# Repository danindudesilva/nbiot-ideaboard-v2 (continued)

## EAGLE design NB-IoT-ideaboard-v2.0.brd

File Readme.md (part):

# Ideamart NB-IoT Ideaboard
###### version 2.0

## Introduction

Ideamart NB-IoT Ideaboard is a connected battery-powered quick-prototyping board created for IoT developers and makers. Its purpose is to make IoT device developemtn process quick and easy as possible. It has communication interfaces such as I2C, SPI, USART, CAN, along with a 12-bit ADC and 16-bit PWM pins broken out with power supply pins, so that any sensor/actuator module in the market can be hooked up to it easily wihout hassle.

It is powered by a 3.7V Li-Ion cell which is managed by an onboard Li-Ion charge controller, making it ideal for prototyping IoT devices. Its main MCU is a powerful STM32F103R series microcontroller with 128K Flash and 20K SRAM memory, enough to make any IoT application effortlessly. It can be connected to the NB-IoT network via a Quectel BC92 modem with 2G GSM fallback option while supporting MFF2 or 3FF eSIM giving it full internet access. 

View 3d model: https://a360.co/3fFFWQ6

## Features
The Ideaboard offers the following features
1.	STM32F103RB microcontroller in LQFP64 package with pin compatibility to any other STM32F103R series microcontroller
2.	Onboard Quectel BC92 BN-IoT modem with 2G GSM fallback
	- LTE Cat NB2: B3/B5/B8/B20/B28
	- GSM: 850/900/1800/1900 MHz
3.	Lithium-Ion cell as primary power supply and onboard Li-Ion management 
    - A 3.7V 2400mAh Li-Ion cell is used to directly power the BC92 modem and the microcontroller
    - Single cell Li-Ion battery management unit for safe charge/discharge of the Li-Ion cell
4.	Flexible power outputs
    - 3.3V power output for basic sensor/actuator power (max usage: 400mA)
    - Optional 5V power output boosted from the 3.7V Li-Ion cell for 5V applications (not available by default)
    - VBUS pins connected to the USB VBUS rail to supply power to the board
5.	External power supply
    - Micro USB port for easy power supply connection
    - External DC 5V source for 2.1 DC connector
6.	Power management access point
    - Connector to an external current meter/ammeter to measure the amount of power drawn from the Li-Ion cell to the Ideaboard
7.	SWD or UART programming
    - Onboard boot mode selection for switching between programming modes
8.	4 LEDs: PWR, USR, NET, and CHG
    - PWR: Board power on indicator
    - USER: User configurable LED
    - NET: BC92 Modem Network status indicator
    - CHG: Li-Ion cell charging indicator
9.	4 pushbuttons: NRST, USER, RESET, PWRKEY
    - NRST: STM32F103RB microcontroller Reset button
    - USER: User configurable pushbutton for input
    - RESET: BC92 modem reset button
    - PWRKEY: BC92 modem power on/off button
10.	Pinheaders to access GPIOs
    - ADC12 IN: 6 GPIOs for 12—bit ADC input
    - I2C 1: GND, SCL, SDA, 3V3 pins for I2C 1 port
    - CAN 1: GND, TX, RX, 3V3 pins for CAN bus port
    - USART 1: VBUS, TXD, RXD, GND, 3V3 pins for USART 1 port
    - SPI 1: 3V3, SCK, MISO, MOSI, NSS, GND pins for SPI 1 interface
    - SPI 2: GND, NSS, MOSI, MISO, SCK, 3V3 pins for SPI 1 interface
    - SWD: SWDIO, GND, SWCLK, 3V3, NRST, SWD pins for SWD programming/debug interface
    - Other GPIOs: A mix of digital and analog I/O pins with no specific assignment for general I/O purposes
11.	Debug UART port for BC92 modem
    - Debug port with VBUS, GND, RX, and TX pins to access the debug COM port of the BC92 modem
12.	eSIM technology or MircoSim compatibility
    - Onboard eSIM MFF2 chip or microsim connector for SIM connection whichever can be used according to user preference
13.	IPEX/u.FL antenna connector for BC92 modem RF antenna
    - Impedance matched to 50 Ohms with optional “PI” type matching circuit reserved for antenna optimization

## STM32F103RB Microcontroller

The STM32F103RB microcontroller is a medium-density performance line family incorporating the high-performance ARM®Cortex®-M3 32-bit RISC core operating at a 72 MHz frequency, high-speed embedded memories with 128K Flash and 20K SRAM (covering from 16 Kbytes to 1 Mbyte of Flash in the STM32F130R line) and an extensive range of enhanced I/Os and peripherals connected to two APB buses. 
All devices in the family offer two 12-bit ADCs, three general purpose 16-bit timers plus one PWM timer, as well as standard and advanced communication interfaces: up to two I2Cs and SPIs, three USARTs, an USB and a CAN.
Key Features
1. ARM 32-bit Cortex -M3 CPU Core
    - 72 MHz maximum frequency,1.25 DMIPS/MHz (Dhrystone 2.1) performance at 0 wait state memory access
    - Single-cycle multiplication and hardware division
2. Memories
    - 128 Kbytes of Flash memory
    - 20 Kbytes of SRAM
    - Clock, reset and supply management
3. 2.0 to 3.6 V application supply and I/Os
    - POR, PDR, and programmable voltage detector (PVD)
    - 8 MHz crystal oscillator
    - Internal 8 MHz factory-trimmed RC
    - Internal 40 kHz RC
    - PLL for CPU clock
    - 32 kHz oscillator for RTC with calibration
4. Low power
    - Sleep, Stop and Standby modes
5. 2 x 12-bit, 1 μs A/D converters
    - Conversion range: 0 to 3.6 V
    - Dual-sample and hold capability
    - Temperature sensor
6. DMA
    - 7-channel DMA controller
    - Peripherals supported: timers, ADC, SPIs, I2Cs and USARTs
7. Debug mode
    - Serial wire debug (SWD)
8. 7 timers
    - Three 16-bit timers, each with up to 4 IC/OC/PWM or pulse counter and quadrature (incremental) encoder input
    - 16-bit, motor control PWM timer with dead-time generation and emergency stop
    - 2 watchdog timers (Independent and Window)
    - SysTick timer 24-bit downcounter
9. Communication interfaces
    - I2C interfaces (SMBus/PMBus)
    - USARTs (ISO 7816 interface, LIN, IrDA capability, modem control)
    - SPIs (18 Mbit/s)
10. CAN interface (2.0B Active)
    - CRC calculation unit, 96-bit unique ID

## Quectel BC92 NB-IoT/GSM modem

BC92 is a high-performance, multi-band NB-IoT/GSM dual-mode module with extremely low power consumption. Designed to be compatible with Quectel GSM/GPRS M95 module, NB-IoT BC95-G module and LPWA BG95 module, BC92 provides abundant external interfaces and protocol stacks, providing great convenience for customers' applications.
BC92 supports 3GPP R13 and R14. Its general features are shown below.
- Support GSM850, EGSM900, DCS1800 and PCS1900
- Support GPRS data transmission and GSM SMS service
- Designed with power-saving technology, the current consumption is as low as 4 μA in deep sleep mode
- Integrate various Internet service protocols (TCP, UDP, PPP, FTP, HTTP(S)
- Support extended AT commands

The frequency bands supported by BC92 are listed below.
- LTE Cat NB2: B3/B5/B8/B20/B28
- GSM: 850/900/1800/1900 MHz

BC92 is an SMD type module with 50 LCC pins, which can be embedded into a variety of data transmission applications with a compact profile of 23.6 mm ×19.9 mm ×2.2 mm, BC92 can meet almost all requirements for M2M applications, such as smoke detector, wireless meter reading, bike sharing, smart parking, asset tracking, wearables, etc.

Power Supply
- Supply voltage range: 3.4~4.2 V.
- Typical supply voltage: 3.8 V.
- Deep Sleep Mode Typical current consumption in Deep Sleep Mode: 4 μA

NB-IoT Frequency Bands
- B3/B5/B8/B20/B28

NB-IoT transmitting power
- 23 dBm ±2 dB

For more information on the STM32F103RB microcontroller or the Quectel BC92 modem, please visit www.st.com or https://www.quectel.com/product/bc92.htm

## QuickStart

The Ideamart NB-IoT Ideaboard is a low-cost and easy-to-use IoT prototyping platform designed for IoT developers and makers which can be used to quickly test and implement a connected IoT solution.  

### Getting started

Follow the sequence below to configure and power up the Ideaboard

1. Make sure a 3.7V Li-Ion battery is connected to the LIPO connector

2. Check the jumper positions on the board
    - Make sure JP1 jumper near the LIPO connector is connected
    - Make sure all 5 of MODEMCTL jumpers are connected parallel to the length of the board
    - Position of the B1 and B0 jumpers of the BOOT MODE selector. (Refer the table on the board or this document to select the boot mode according to your programming preference)

3. Connect the Ideaboard to a PC or a 5V power adapter with a micro USB cable through the POWER USB connector or using a 5V DC power supply through to the 2.1mm barrel connector on the bottom side of the board. The CHG LED will turn on indicating that the Li-Ion cell is charging. 

4. Turn the power switch on. The PWR LED will turn on indicating that Ideaboard is getting power from the Li-Ion cell.

## Hardware layout and configuration

The Ideaboard is designed around the STM32F103RB MCU in a 64-pin LQFP package as the main controller.

### Hardware block diagram

#### Top Layout

#### Bottom Layout

### Ideaboard mechanical dimensions

### Pinout Diagram

### Power supply and Battery Management

The Ideaboard’s main power supply is it’s 3.7V Li-Ion cell. It must always be connected although an external power source is used. The external power supply charges the Li-Ion cell while the cell powers the board. 
The power switch must be turned on to get power to the board. Then the PWR LED will turn on.  When as external power supply is connected, the battery will start charging and it will be indicated by the CHG LED. 
The external power supply must be 5V and can be connected to the POWER micro USB port or the 5V DC input jack on the bottom side of the PCB.

The 3.3V rail is powered by a 3.3V LDO which is directly connected to the Li-Ion cell. An optional 5V step-up converter is also powered by the Li-Ion cell for any external 5V peripherals.

#### Powering external peripherals using the Ideaboard

3.3V peripherals can be connected to the 3V3 pins on the Ideaboard for power.For 5V peripherals, the 5V pins on the Ideaboard can be used. These pins will not have power unless the 5V step-up converter on the bottom side of the Ideaboard is soldered. 

The VBUS pins can also be used to provide 5V power to external peripherals, but it is not recommended since the VBUS rail will lose power once the external power is removed, therefore, use the 5V step-up converter. 

All the VBUS pins are connected to the VBUS of the USB port and the positive terminal of the 5V DC input.

#### Using the onboard 5V step-up converter

The 5V step-up converter is soldered by default. Please refer the below table when assembling the parts for the 5V step-up converter.
| Designator | Value | Component | Package | Manufacturer Part # |
| ----------- | ----------- | ----------- |----------- |----------- |
|   U4      |   PAM2401 |   Step-up converter	|   MSOP8	    |PAM2401SCADJ   |
|   C20     |   22uF    |   Ceramic Capacitor   |   0805 SMD    |   -           |
|   C21     |   22uF    |   Ceramic Capacitor   |   0805 SMD    |   -           |
|   R14     |   750k    |   Resistor            |   0805 SMD    |   -           |
|   R15     |   750k    |   Resistor            |   0805 SMD    |   -           |
|   R16     |   100k    |   Resistor            |   0805 SMD    |   -           |
|   L2      |   2.2uH/3A|   Inductor            |   4x4mm SMD   |IFSC1515AHER2R2M01|

#### Measuring the Ideaboard’s power consumption

The power consumption can be measured by connecting an ammeter to the JP1 pins on the ideaboard. This will give the current drawn from the Li-Ion cell by the Ideaboard and the connected peripherals. 

Once the current measuring device is removed, the jumper must be put back on the JP1 pins in order for the Ideaboard to work.

#### LEDs and Pushbuttons

The ideaboard has 4 LEDs and 4 pushbuttons 
##### LEDs
- PWR: Power on indicator.
- USR: An LED connected to PB13 pin of the MCU
- CHG: Li-Ion cell charging indicator
- NET: Network status of the BC92 modem

##### Pushbuttons
- USER: A pushbutton connected to PC13 pin of the MCU
- NRST: Reset pin of the STM32F103RB MCU
- PWRKEY: Powerkey button for the BC92 modem. 
- RESET: Reset button for the BC92 modem

### NB-IoT Modem Communication

The STM32F103RB MCU communicates with the Quectel BC92 modem through a UART port. 
The modem is connected to USART3 of the MCU. The control signals to the modem from the MCU are PSM_EINT, POWERKEY, and RESET. 
All the UART and control signals are connected to the MCU via jumpers in case the developer needs to disconnect the modem communication or control signals from the MCU. Please refer the below figure for the connections.

### CC1101 connector

The Ideaboard has a 2.54mm pitch 2x6 female pinheader connector for a CC1101 radio module. This is connected to the MCUs SPI1 port. Please refer below figure for the pin connections.

## Programming the Ideaboard

Ideaboard can be programmed using its SWD or USART1 interface. The 2 programming interfaces are highlighted on the top side of the PCB in white. In order to use either programming mode, the boot mode of the MCU must be selected by setting the B0 and B1 jumpers on BOOT pin header as given in the table below.

| BOOT0 |   BOOT1   | Boot mode         | Aliasing  |
| ----- | --------- | ---------         | --------  |
|  x    |       0   | Main Flash Memory | Main flash memory is selected as boot space   |
|  0    |       1   | System Memory     | System Memory is selected as boot space       |
|  1    |       1   | Embedded SRAM     | Embedded SRAM is selected as boot space       |

### Using the SWD Interface

The main flash memory is used as boot space. To select the boot mode of the MCU, set the BOOT jumpers as below:

````
B0 = 0 and B1 = 0
````

After setting the jumpers Reset the MCU.

When using the SWD interface, an external ST-Link programmer such as ST-Link V2 dongle can be used.

The pins 2, 4, and 6 on the ST-Link V2 programmer should be connected to SWCLK, SWDIO, and GND on the Ideaboard SWD pin header respectively.

### Using the USART 1 Interface

When using the USART1 interface, the boot loader in the system memory must be activated. Set the BOOT jumpers as below. This embedded boot loader is programmed by ST during production.

The system memory is used as boot space. To select the boot mode of the MCU, set the BOOT jumpers as below:
````
B0 = 1 and B1 = 0
````

After setting the jumpers Reset the MCU.

In order to use the USART1 interface, a USB to serial converter should be used by connecting it to the RXD, TXD, and GND pins of the Ideaboard. (The VBUS pin can be used to charge the Li-Ion cell if needed).

After installing the STM32 board definitions, Arduino IDE can be used to program the Ideaboard using the USART1 interface.

### Using the CDC Virtual com port

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
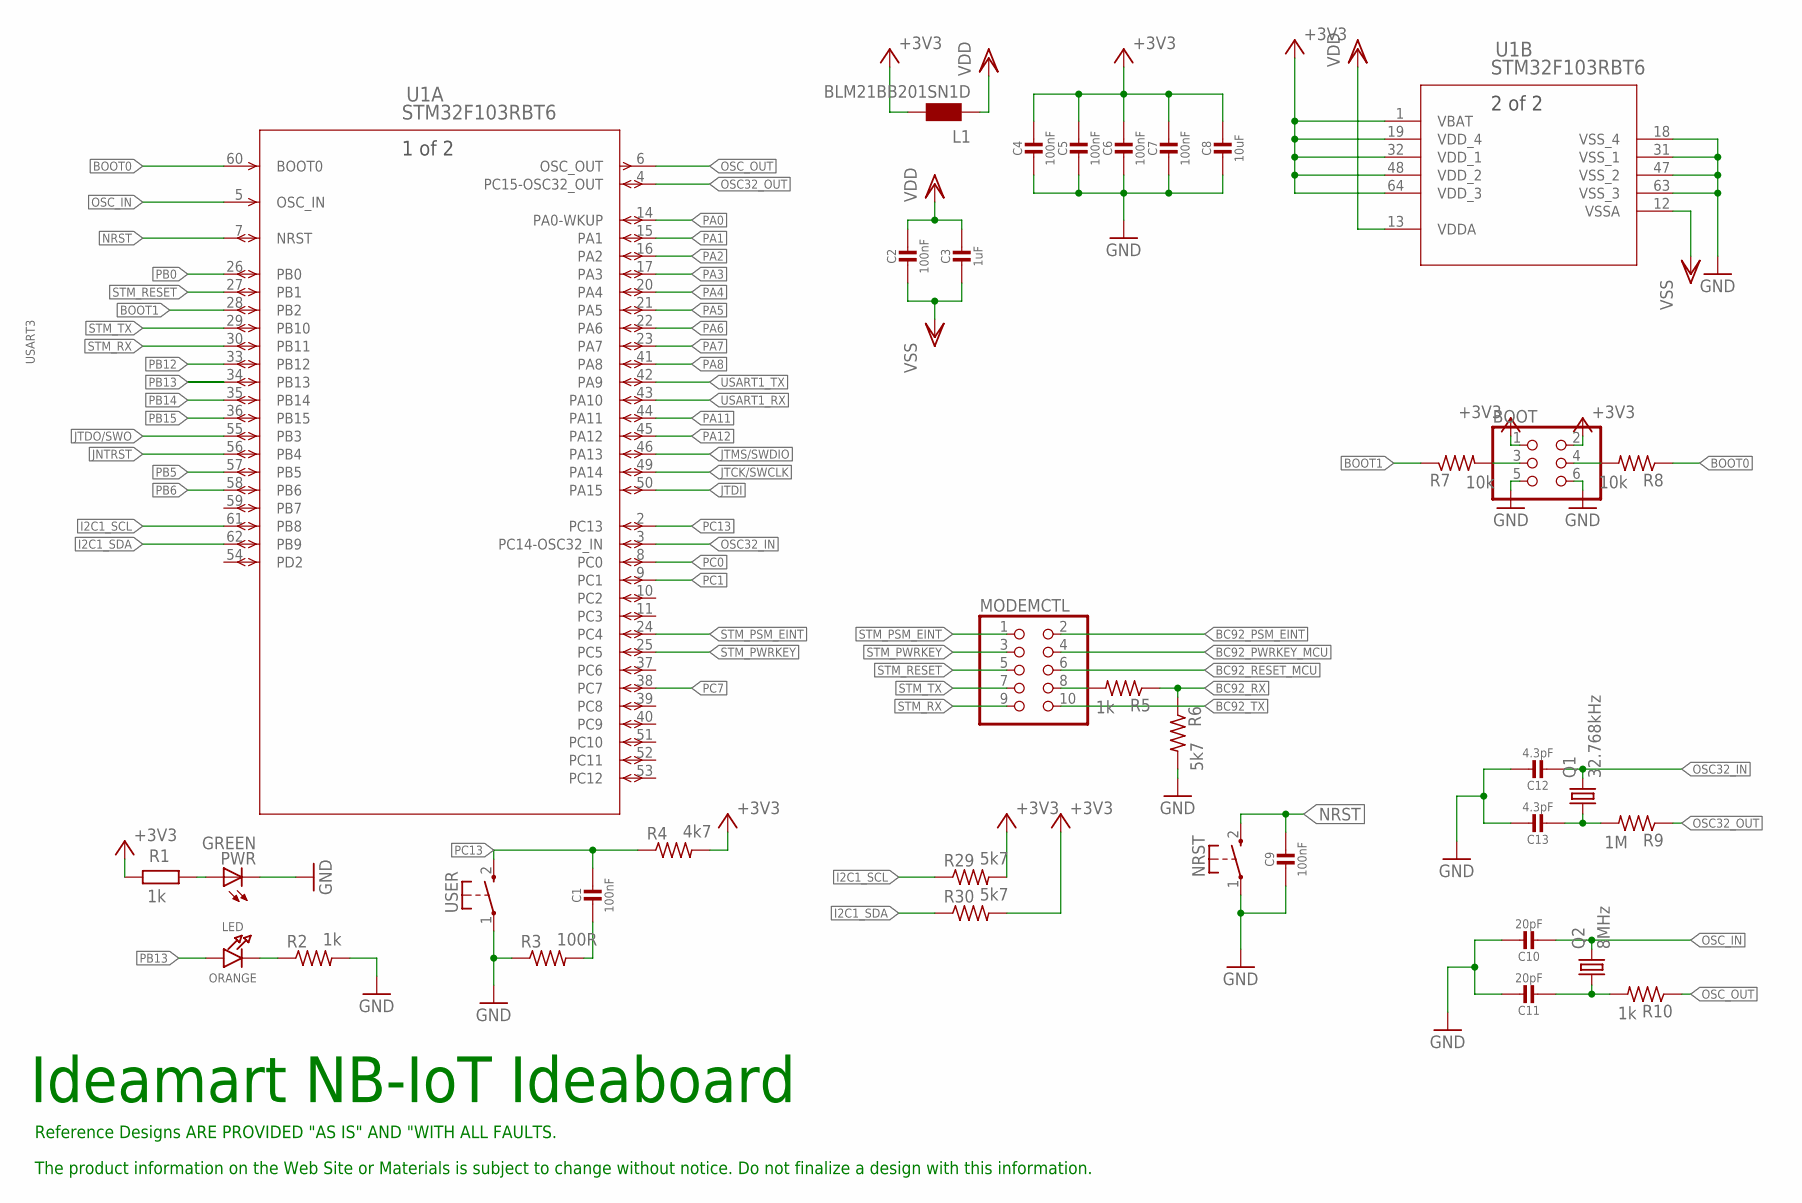
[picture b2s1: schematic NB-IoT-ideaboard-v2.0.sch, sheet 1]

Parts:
BOOT: PINHD-2X03_2.54-SMD; 2X03SMD
C1, C2, C4, C5, C6, C7, C9: 100nF; _0805MP
C3: 1uF; _0805MP
C8: 10uF; _0805MP
C10, C11: 20pF; _0805MP
C12, C13: 4.3pF; _0805MP
L1: BLM21BB201SN1D; 0805
LED: ORANGE; CHIPLED_0805
MODEMCTL: PINHD-2X05_2.54-SMD; 2X05SMD
NRST: KSS-2EG4430
PWR: GREEN; CHIP-LED0805
Q1: 32.768kHz; TC26H-SMD
Q2: 8MHz; SM49
R1: 1k; R0805
R2, R5, R10: 1k; M0805
R3: 100R; M0805
R4: 4k7; M0805
R6, R29, R30: 5k7; M0805
R7, R8: 10k; M0805
R9: 1M; M0805
U1: STM32F103RBT6; LQFP64-10X10MM
USER: KSS-2EG4430

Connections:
+3V3: BOOT.1, BOOT.2, C4.1, C5.1, C6.1, C7.1, C8.1, L1.2, R1.2, R4.2, R29.2, R30.2, U1.1 (VBAT), U1.19 (VDD_4), U1.32 (VDD_1), U1.48 (VDD_2), U1.64 (VDD_3); also elsewhere on the board
BC92_PSM_EINT: MODEMCTL.2; also elsewhere on the board
BC92_PWRKEY_MCU: MODEMCTL.4; also elsewhere on the board
BC92_RESET_MCU: MODEMCTL.6; also elsewhere on the board
BC92_RX: R5.1, R6.1; also elsewhere on the board
BC92_TX: MODEMCTL.10; also elsewhere on the board
BOOT0: R8.1, U1.60 (BOOT0)
BOOT1: R7.1, U1.28 (PB2)
GND: BOOT.5, BOOT.6, C4.2, C5.2, C6.2, C7.2, C8.2, C9.2, C10.1, C11.1, C12.1, C13.1, NRST.1, PWR.C, R2.2, R3.1, R6.2, U1.18 (VSS_4), U1.31 (VSS_1), U1.47 (VSS_2), U1.63 (VSS_3), USER.1; also elsewhere on the board
I2C1_SCL: R29.1, U1.61 (PB8); also elsewhere on the board
I2C1_SDA: R30.1, U1.62 (PB9); also elsewhere on the board
JNTRST: U1.56 (PB4); also elsewhere on the board
JTCK/SWCLK: U1.49 (PA14); also elsewhere on the board
JTDI: U1.50 (PA15)
JTDO/SWO: U1.55 (PB3); also elsewhere on the board
JTMS/SWDIO: U1.46 (PA13); also elsewhere on the board
unnamed: BOOT.3, R7.2
unnamed: PWR.A, R1.1
unnamed: C11.2, Q2.1, R10.2
unnamed: C13.2, Q1.P$1 (1), R9.2
unnamed: C1.2, R3.2
unnamed: BOOT.4, R8.2
unnamed: LED.C, R2.1
unnamed: MODEMCTL.8, R5.2
NRST: C9.1, NRST.2 (S), U1.7 (NRST); also elsewhere on the board
OSC32_IN: C12.2, Q1.P$2 (2), U1.3 (PC14-OSC32_IN)
OSC32_OUT: R9.1, U1.4 (PC15-OSC32_OUT)
OSC_IN: C10.2, Q2.2, U1.5 (OSC_IN)
OSC_OUT: R10.1, U1.6 (OSC_OUT)
PA0: U1.14 (PA0-WKUP); also elsewhere on the board
PA1: U1.15 (PA1); also elsewhere on the board
PA2: U1.16 (PA2); also elsewhere on the board
PA3: U1.17 (PA3); also elsewhere on the board
PA4: U1.20 (PA4); also elsewhere on the board
PA5: U1.21 (PA5); also elsewhere on the board
PA6: U1.22 (PA6); also elsewhere on the board
PA7: U1.23 (PA7); also elsewhere on the board
PA8: U1.41 (PA8); also elsewhere on the board
PA11: U1.44 (PA11); also elsewhere on the board
PA12: U1.45 (PA12); also elsewhere on the board
PB0: U1.26 (PB0); also elsewhere on the board
PB5: U1.57 (PB5); also elsewhere on the board
PB6: U1.58 (PB6); also elsewhere on the board
PB12: U1.33 (PB12); also elsewhere on the board
PB13: LED.A, U1.34 (PB13); also elsewhere on the board
PB14: U1.35 (PB14); also elsewhere on the board
PB15: U1.36 (PB15); also elsewhere on the board
PC0: U1.8 (PC0); also elsewhere on the board
PC1: U1.9 (PC1); also elsewhere on the board
PC7: U1.38 (PC7); also elsewhere on the board
PC13: C1.1, R4.1, U1.2 (PC13), USER.2 (S)
STM_PSM_EINT: MODEMCTL.1, U1.24 (PC4)
STM_PWRKEY: MODEMCTL.3, U1.25 (PC5)
STM_RESET: MODEMCTL.5, U1.27 (PB1)
STM_RX: MODEMCTL.9, U1.30 (PB11)
STM_TX: MODEMCTL.7, U1.29 (PB10)
USART1_RX: U1.43 (PA10); also elsewhere on the board
USART1_TX: U1.42 (PA9); also elsewhere on the board
VDD: C2.1, C3.1, L1.1, U1.13 (VDDA); also elsewhere on the board
VSS: C2.2, C3.2, U1.12 (VSSA)

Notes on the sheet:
Ideamart NB-IoT Ideaboard
Reference Designs ARE PROVIDED "AS IS" AND "WITH ALL FAULTS.
The product information on the Web Site or Materials is subject to change without notice. Do not finalize a design with this information.
USART3

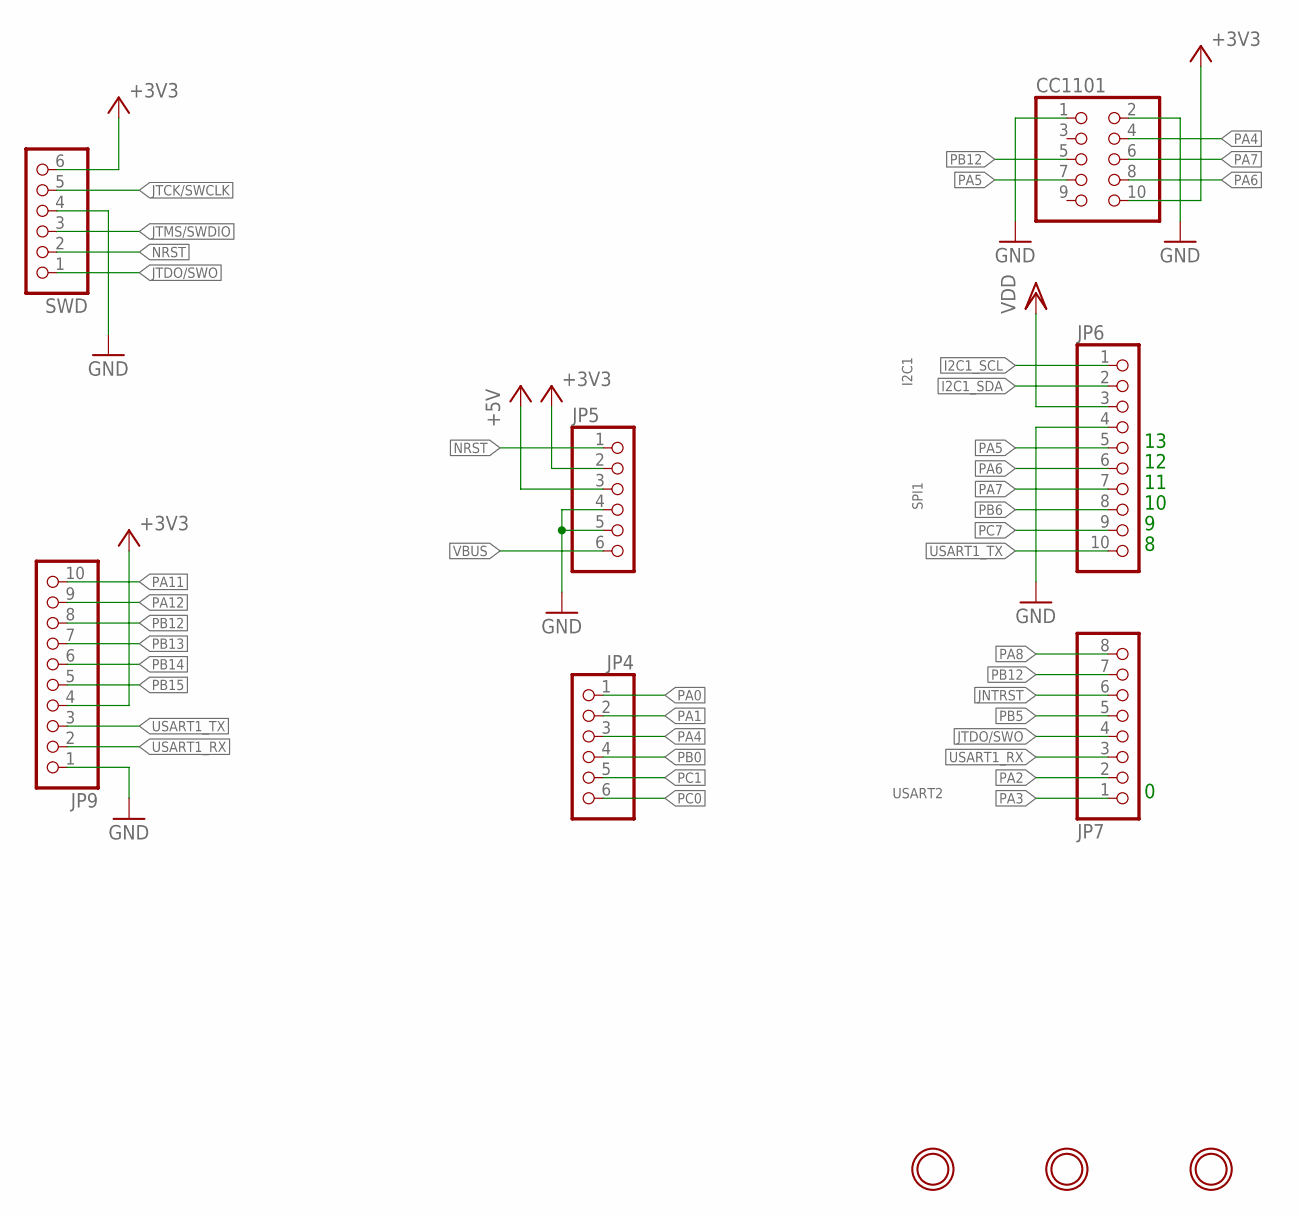
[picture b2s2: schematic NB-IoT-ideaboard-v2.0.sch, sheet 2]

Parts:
$H1, $H2, $H3: MOUNTINGHOLE3.0THIN; MOUNTINGHOLE_3.0_PLATEDTHIN
CC1101: PINHD-2X05_2.54-SMD; 2X05SMD
JP4, JP5: PINHD-1X6; 1X06
JP6: PINHD-1X10; 1X10
JP7: PINHD-1X8; 1X08
JP9: PINHD-1X10_2.54-S; 1X10-S
SWD: PINHD-1X6; 1X06

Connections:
+3V3: CC1101.10, JP5.2, JP9.4, SWD.6; also elsewhere on the board
+5V: JP5.3; also elsewhere on the board
GND: CC1101.1, CC1101.2, JP5.4, JP5.5, JP6.4, JP9.1, SWD.4; also elsewhere on the board
I2C1_SCL: JP6.1; also elsewhere on the board
I2C1_SDA: JP6.2; also elsewhere on the board
JNTRST: JP7.6; also elsewhere on the board
JTCK/SWCLK: SWD.5; also elsewhere on the board
JTDO/SWO: JP7.4, SWD.1; also elsewhere on the board
JTMS/SWDIO: SWD.3; also elsewhere on the board
NRST: JP5.1, SWD.2; also elsewhere on the board
PA0: JP4.1; also elsewhere on the board
PA1: JP4.2; also elsewhere on the board
PA2: JP7.2; also elsewhere on the board
PA3: JP7.1; also elsewhere on the board
PA4: CC1101.4, JP4.3; also elsewhere on the board
PA5: CC1101.7, JP6.5; also elsewhere on the board
PA6: CC1101.8, JP6.6; also elsewhere on the board
PA7: CC1101.6, JP6.7; also elsewhere on the board
PA8: JP7.8; also elsewhere on the board
PA11: JP9.10; also elsewhere on the board
PA12: JP9.9; also elsewhere on the board
PB0: JP4.4; also elsewhere on the board
PB5: JP7.5; also elsewhere on the board
PB6: JP6.8; also elsewhere on the board
PB12: CC1101.5, JP7.7, JP9.8; also elsewhere on the board
PB13: JP9.7; also elsewhere on the board
PB14: JP9.6; also elsewhere on the board
PB15: JP9.5; also elsewhere on the board
PC0: JP4.6; also elsewhere on the board
PC1: JP4.5; also elsewhere on the board
PC7: JP6.9; also elsewhere on the board
USART1_RX: JP7.3, JP9.2; also elsewhere on the board
USART1_TX: JP6.10, JP9.3; also elsewhere on the board
VBUS: JP5.6; also elsewhere on the board
VDD: JP6.3; also elsewhere on the board

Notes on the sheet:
I2C1
SPI1
USART2

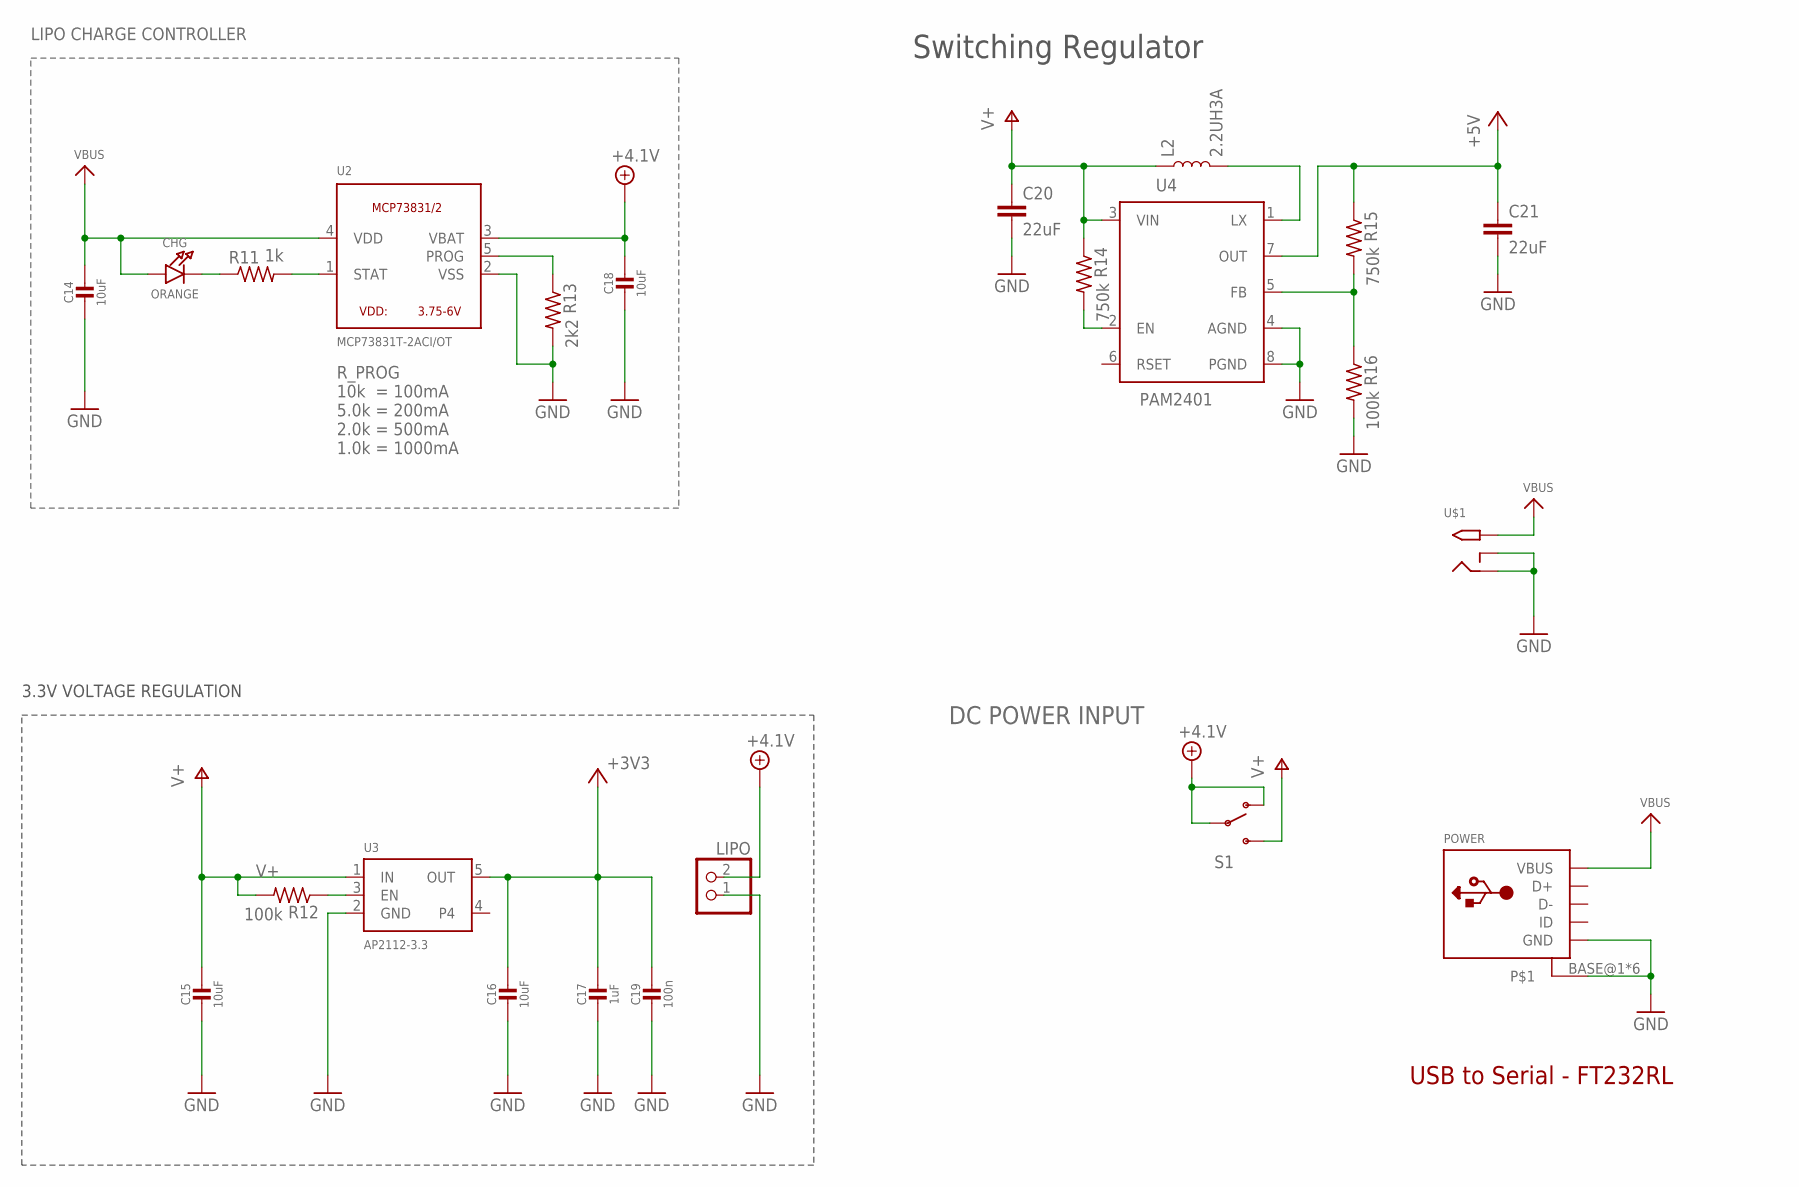
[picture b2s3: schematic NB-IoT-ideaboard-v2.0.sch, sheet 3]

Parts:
C14, C18: 10uF; _0805
C15, C16: 10uF; _0805MP
C17: 1uF; _0805MP
C19: 100n; _0805MP
C20, C21: 22uF; 0805
CHG: ORANGE; CHIPLED_0805
L2: 2.2UH3A; INDUCTOR_4X4MM
LIPO: JST_2PIN-SMT; JST-PH-2-SMT
POWER: USB_MICRO_20329_V2; 4UCONN_20329_V2
R11: 1k; M0805
R12, R16: 100k; M0805
R13: 2k2; M0805
R14, R15: 750k; M0805
S1: SWITCH-SPDT-SMD-A; SWITCH-SPST-SMD-A
U2: MCP73831T-2ACI/OT; SOT23-5
U3: AP2112-3.3; SOT23-5
U4: PAM2401; MSOP8
U$1: 2.1MMJACKSMT; DCJACK_2MM_SMT

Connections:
+3V3: C16.1, C17.1, C19.1, U3.5 (OUT); also elsewhere on the board
+4.1V: C18.1, LIPO.2 (1), S1.1 (O), S1.2, U2.3 (VBAT)
+5V: C21.1, R15.1, U4.7 (OUT); also elsewhere on the board
EN: R14.2, U4.2 (EN)
GND: C14.2, C15.2, C16.2, C17.2, C18.2, C19.2, C20.2, C21.2, LIPO.1 (2), POWER.BASE@1, POWER.BASE@2, POWER.GND, POWER.SPRT@1, POWER.SPRT@2, POWER.SPRT@3, POWER.SPRT@4, R13.2, R16.2, U2.2 (VSS), U3.2 (GND), U4.4 (AGND), U4.8 (PGND), U$1.GND (RING), U$1.GNDBREAK (RING_SW); also elsewhere on the board
unnamed: R12.1, U3.3 (EN)
unnamed: CHG.C, R11.1
unnamed: R11.2, U2.1 (STAT)
unnamed: R13.1, U2.5 (PROG)
unnamed: R15.2, R16.1, U4.5 (FB)
unnamed: L2.P$2 (2), U4.1 (LX)
V+: C15.1, C20.1, L2.P$1 (1), R12.2, R14.1, S1.3 (S), U3.1 (IN), U4.3 (VIN); also elsewhere on the board
VBUS: C14.1, CHG.A, POWER.VBUS, U2.4 (VDD), U$1.PWR2 (TIP); also elsewhere on the board

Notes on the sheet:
USB to Serial - FT232RL
3.3V VOLTAGE REGULATION
R_PROG 10k = 100mA 5.0k = 200mA 2.0k = 500mA 1.0k = 1000mA
LIPO CHARGE CONTROLLER
Switching Regulator
DC POWER INPUT

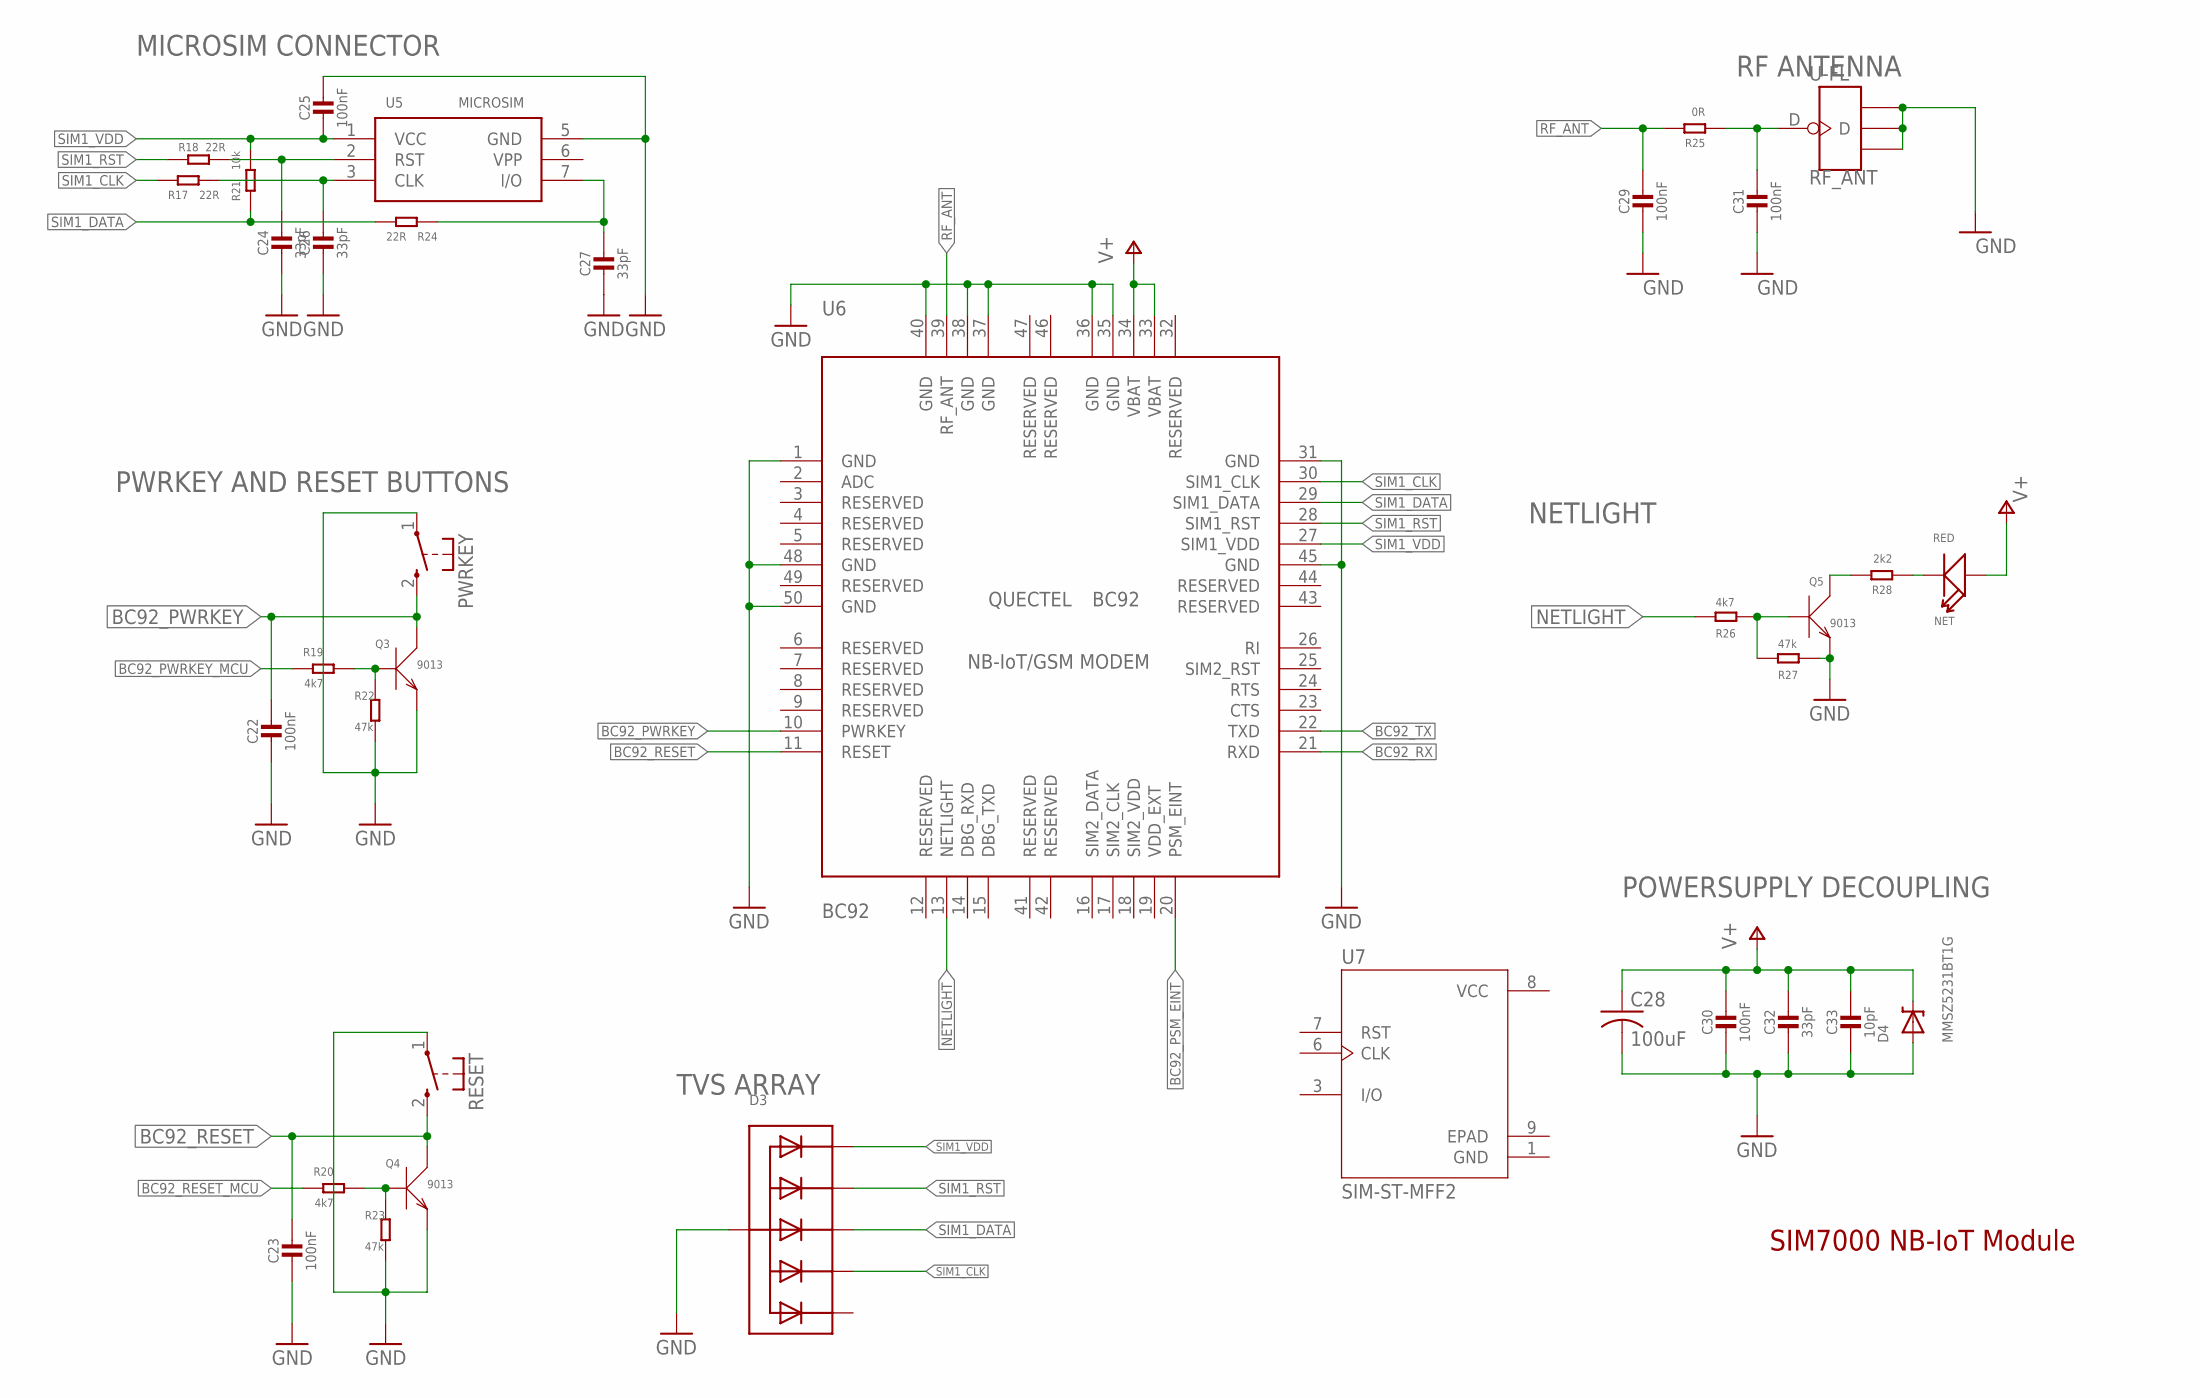
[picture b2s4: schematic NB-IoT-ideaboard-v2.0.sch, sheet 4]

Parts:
C22, C23, C25, C29, C30, C31: 100nF; _0805
C24, C26, C27, C32: 33pF; _0805
C28: 100uF; C1210
C33: 10pF; _0805
D3: TVSARRAY_5LANE; SOT363
D4: MMSZ5231BT1G; SOD-123
NET: RED; LED-0805
PWRKEY: KSS-2EG4430
Q3, Q4, Q5: 9013; SOT23
R17, R18, R24: 22R; 0805
R19, R20, R26: 4k7; 0805
R21: 10k; 0805
R22, R23, R27: 47k; 0805
R25: 0R; 0805
R28: 2k2; 0805
RESET: KSS-2EG4430
RF_ANT: U-FL; 4P-U-FL
U5: MICROSIM
U6: BC92
U7: SIM-ST-MFF2; PSON127P500X600X82-9N

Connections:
BC92_PSM_EINT: U6.20 (PSM_EINT); also elsewhere on the board
BC92_PWRKEY: C22.1, PWRKEY.2 (S), Q3.3 (C), U6.10 (PWRKEY)
BC92_PWRKEY_MCU: R19.1; also elsewhere on the board
BC92_RESET: C23.1, Q4.3 (C), RESET.2 (S), U6.11 (RESET)
BC92_RESET_MCU: R20.1; also elsewhere on the board
BC92_RX: U6.21 (RXD); also elsewhere on the board
BC92_TX: U6.22 (TXD); also elsewhere on the board
GND: C22.2, C23.2, C24.2, C25.1, C26.2, C27.2, C28.2, C29.2, C30.2, C31.2, C32.2, C33.2, D3.2 (A), D4.A, PWRKEY.1, Q3.2 (E), Q4.2 (E), Q5.2 (E), R22.2, R23.2, R27.2, RESET.1, RF_ANT.GND1, RF_ANT.GND2, RF_ANT.GND3, U5.5 (GND), U6.1 (GND), U6.31 (GND), U6.35 (GND), U6.36 (GND), U6.37 (GND), U6.38 (GND), U6.40 (GND), U6.45 (GND), U6.48 (GND), U6.50 (GND), U7.1 (GND); also elsewhere on the board
unnamed: C31.1, R25.1, RF_ANT.D
unnamed: C27.1, R24.1, U5.7 (I/O)
unnamed: C26.1, R17.1, U5.3 (CLK)
unnamed: C24.1, R18.1, U5.2 (RST)
unnamed: Q4.1 (B), R20.2, R23.1
unnamed: Q5.3 (C), R28.2
unnamed: NET.-, R28.1
unnamed: Q5.1 (B), R26.2, R27.1
unnamed: Q3.1 (B), R19.2, R22.1
NETLIGHT: R26.1, U6.13 (NETLIGHT)
RF_ANT: C29.1, R25.2, U6.39 (RF_ANT)
SIM1_CLK: D3.5 (C4), R17.2, U6.30 (SIM1_CLK)
SIM1_DATA: D3.4 (C3), R21.1, R24.2, U6.29 (SIM1_DATA)
SIM1_RST: D3.3 (C2), R18.2, U6.28 (SIM1_RST)
SIM1_VDD: C25.2, D3.1 (C1), R21.2, U5.1 (VCC), U6.27 (SIM1_VDD)
V+: C28.1, C30.1, C32.1, C33.1, D4.C, NET.+, U6.33 (VBAT), U6.34 (VBAT); also elsewhere on the board
VCC: U7.8 (VCC)

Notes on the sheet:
TVS ARRAY
MICROSIM CONNECTOR
SIM7000 NB-IoT Module
NETLIGHT
RF ANTENNA
PWRKEY AND RESET BUTTONS
POWERSUPPLY DECOUPLING

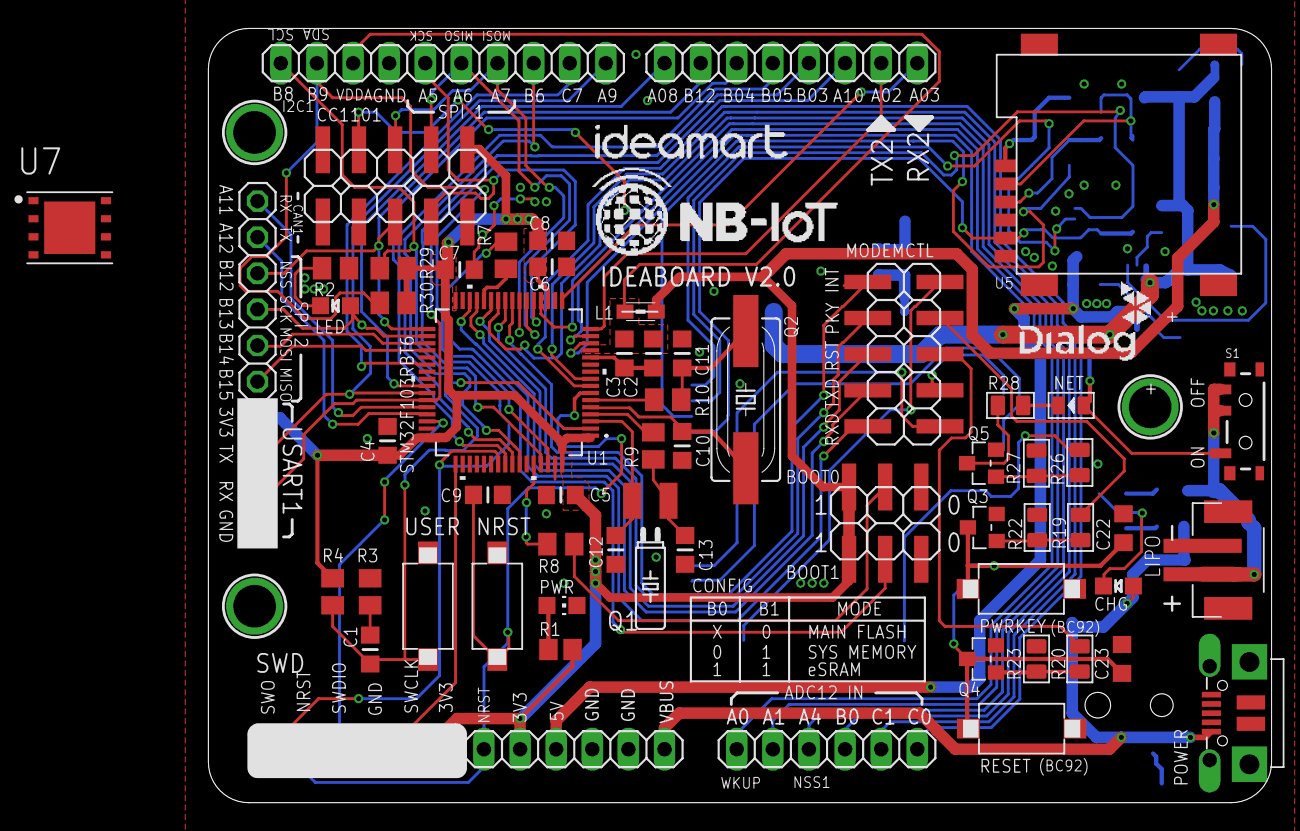
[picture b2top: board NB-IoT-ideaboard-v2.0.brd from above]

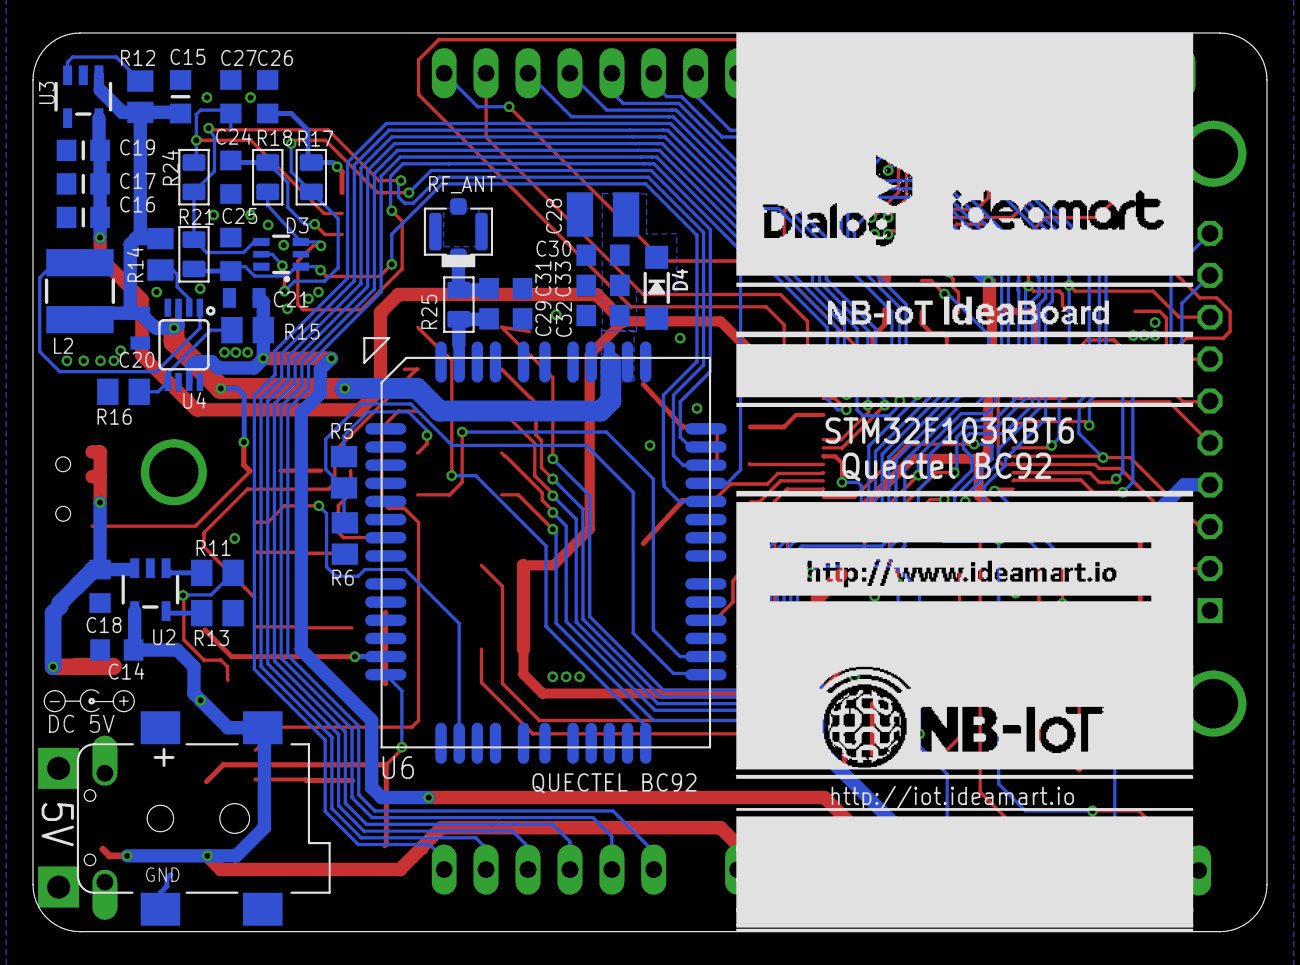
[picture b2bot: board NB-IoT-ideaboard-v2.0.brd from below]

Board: 2 copper layers, 74.8 x 54.5 mm, 104 parts (40 on the bottom side), 87 nets.

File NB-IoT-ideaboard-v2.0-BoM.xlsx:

Qty | Value | Device | Package | Parts | Description | COMMENTS | MANUFACTURER_PART_NUMBER | VENDOR
1 |  | JST_2PIN-SMT | JST-PH-2-SMT | LIPO | JST 2-Pin Connector for LiPo Battery |  | S2B-ZR-SM4A-TF(LF)(SN) | LCSC
1 |  | PINHD-1X10 | 1X10 | JP6 | PIN HEADER | DO NOT SOLDER |  | LCSC
1 |  | PINHD-1X10_2.54-S | 1X10-S | JP9 | PIN HEADER | DO NOT SOLDER |  | LCSC
3 |  | PINHD-1X6 | 1X06 | JP4, JP5, SWD | PIN HEADER | DO NOT SOLDER |  | LCSC
1 |  | PINHD-1X8 | 1X08 | JP7 | PIN HEADER | DO NOT SOLDER |  | LCSC
1 |  | PINHD-2X03_2.54-SMD | 2X03SMD | BOOT | PIN HEADER SMD MALE | MALE | C124390 | LCSC
1 |  | PINHD-2X05_2.54-SMD | 2X05SMD | CC1101 | PIN HEADER SMD FEMALE | FEMALE | 2543U-205CNG1MNT01 | LCSC
1 |  | PINHD-2X05_2.54-SMD | 2X05SMD | MODEMCTL | PIN HEADER SMD MALE | MALE | C124391 | LCSC
1 |  | SWITCH-SPST-SMD-A | SWITCH-SPST-SMD-A | S1 | SPDT Switch | At least 300mA | SSSS811101 | LCSC
1 |  | TVSARRAY_5LANE | SOT363 | D3 | Voltage Transient Suppressor Array |  | SM15C | LCSC
1 |  | USB_MICRO_20329_V2 | 4UCONN_20329_V2 | POWER | USB Connectors |  | U254-051T-4BH83-F1S | LCSC
1 | 100R | R-US_M0805 | M0805 | R3 | RESISTOR, American symbol |  | RT0805BRE07100RL | LCSC
2 | 100k | R-US_M0805 | M0805 | R12, R16 | RESISTOR, American symbol |  | RT0805CRE07100KL | LCSC
14 | 100nF | CAP_CERAMIC_0805 | _0805 | C1, C2, C4, C5, C6, C7, C9, C19, C22, C23, C25, C29, C30, C31 | Ceramic Capacitors |  | AC0805KRX7R9BB104 | LCSC
1 | 100uF | C-USC1210 | C1210 | C28 | CAPACITOR, American symbol |  | GRM32ER60J107ME20L | LCSC
3 | 10k | R-0805 | 0805 | R7, R8, R21 | RESISTOR, American symbol |  | RT0805WRD0710KL | LCSC
1 | 10pF | CAP_CERAMIC_0805 | _0805 | C33 | Ceramic Capacitors |  | CC0805FRNPO9BN100 | LCSC
5 | 10uF | CAP_CERAMIC_0805 | _0805 | C8, C15, C16, C14, C18 | Ceramic Capacitors |  | CC0805KKX5R7BB106 | LCSC
1 | 1M | R-US_M0805 | M0805 | R9 | RESISTOR, American symbol |  | RT0805BRD071ML | LCSC
3 | 1k | R-US_M0805 | M0805 | R5, R10, R11 | RESISTOR, American symbol |  | RT0805CRE071KL | LCSC
2 | 1uF | CAP_CERAMIC_0805MP | _0805MP | C3, C17 | Ceramic Capacitors |  | CC0805KKX5R9BB105 | LCSC
1 | 2.1MMJACKSMT | 2.1MMJACKSMT | DCJACK_2MM_SMT | U$1 | Digikey part #PJ-102A, 4UCON part #05537 |  | DC-005-5A-2.5-SMT | LCSC
1 | 2.2UH3A | INDUCTOR | INDUCTOR_4X4MM | L2 | Inductors |  | IFSC1515AHER2R2M01 | LCSC
2 | 2k2 | R-US_M0805 | M0805 | R13, R28 | RESISTOR, American symbol |  | AC0805FR-072K2L | LCSC
2 | 20pF | CAP_CERAMIC_0805MP | _0805MP | C10, C11 | Ceramic Capacitors |  | CC0805GRNPO9BN200 | LCSC
3 | 22R | R-0805 | 0805 | R17, R18, R24 | RESISTOR, American symbol |  | RC0805JR-0722RL | LCSC
2 | 22uF | 22UF-0805-10V-20% | 0805 | C20, C21 | Ceramic Capacitors |  | CC0805MKX5R5BB226 | LCSC
1 | 32.768kHz | CRYSTALTC26H-SMD | TC26H-SMD | Q1 | CRYSTAL |  | Q11C02RX1001300 | LCSC
2 | 330R | R-US_M0805 | M0805 | R1, R2 | RESISTOR, American symbol |  | RC0805FR-0722RL | LCSC
4 | 33pF | CAP_CERAMIC_0805 | _0805 | C24, C26, C27, C32 | Ceramic Capacitors |  | CC0805JRNPO9BN330 | LCSC
2 | 4.3pF | CAP_CERAMIC_0805MP | _0805MP | C12, C13 | Ceramic Capacitors | Could not find 4.3pF so mentioned 4.7pF | CC0805BRNPO9BN4R7 | LCSC
3 | 47k | R-0805 | 0805 | R22, R23, R27 | RESISTOR, American symbol |  | RT0805CRE0747KL | LCSC
4 | 4k7 | R-US_M0805 | M0805 | R4, R19, R20, R26 | RESISTOR, American symbol |  | RT0805CRE074K7L | LCSC
1 | 5k7 | R-US_M0805 | M0805 | R6 | RESISTOR, American symbol |  | AC0805FR-075K76L | LCSC
2 | 750k | R-US_M0805 | M0805 | R14, R15 | RESISTOR, American symbol |  | RC0805FR-07750KL | LCSC
1 | 8MHz | CRYSTALSM49 | SM49 | Q2 | CRYSTAL |  | C08000J060 | LCSC
3 | s9013 | TRANSISTOR-NPN-SOT23 | SOT23 | Q3, Q4, Q5 | NPN audion |  | S9013G | LCSC
1 | AP2112-3.3 | VREG_SOT23-5 | SOT23-5 | U3 | SOT23-5 Fixed Voltage Regulators |  | AP2112K-3.3TRG1 | LCSC
1 | BC92 | BC92 | BC92 | U6 | Quectel BC92 Module |  |  | Quectel
1 | BLM21BB201SN1D | WE-CBF_0805 | 0805 | L1 | SMD EMI Suppression Ferrite Beads |  | BLM21BB201SN1D | LCSC
4 | KSS-2EG4430 | KSS-2EG4430 | KSS-2EG4430 | NRST, PWRKEY, RESET, USER | Size: 3x6mm |  | 1TS002E-2500-2500-CT | LCSC
1 | MCP73831T-2ACI/OT | MCP73831/2 | SOT23-5 | U2 | MCP73831/2 LIPO Charger |  | MCP73831T-2ACI/OT | LCSC
1 | MICROSIM | MICROSIM | MICROSIM | U5 | Micro SIM Card Connector |  | SMC-202-6 | LCSC
1 | MMSZ5231BT1G | DIODE-ZENERSOD123 | SOD-123 | D4 | Zener Diode |  | MMSZ5231BT1G | LCSC
5 | LED_SMD | LED0805 | CHIPLED_0805 | PWR,LED, CHG, LED, NET | LED |  | 17-21SURC/S530-A3/TR8 | LCSC
1 | PAM2401 | PAM2401 | MSOP8 | U4 | PAM2401 - Boost PMIC |  | PAM2401SCADJ | LCSC
1 | STM32F103RBT6 | STM32F103RBT6 | LQFP64-10X10MM | U1 | Microcontroller |  | STM32F103RBT6 | LCSC
1 | IPEX Connector | ANTENNA-U-FL | 4P-U-FL | RF_ANT | Antenna connector |  | KH-IPEX4-2020 | LCSC

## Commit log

2020-10-31 Design files
2020-11-01 Adds logos, mounting holes
2020-11-01 Minor changes
2020-11-03 Adjust USB port
2020-11-05 JLCPCB layout started
2020-11-05 JLCPCB layout finished
2020-11-06 JLCPCB layout tweaks
2020-11-06 JLCPCB layout SILK EDITS
2020-11-06 JLCPCB layout antenna layout edits
2020-11-06 JLCPCB layout antenna silkscreen edits
2020-11-06 JLCPCB LED placements changed
2020-11-08 JLCPCB header position changes
2020-11-08 JLCPCB SVG images
2020-11-09 Readme.md
2020-11-09 image edit
2020-11-10 Adds USB FS data lines for CDC Virtual Com port
2020-11-13 Finalizing manufacturing files and 3D model
2020-11-13 Changes to BoM
2020-11-13 Enclosure 3D model
2020-11-13 Readme
2020-11-14 Readme cover image
2020-11-16 Adds cable gland, sma connector to enclosure
2020-11-16 New enclosure images
2020-11-19 Crystal RC values updated. New pcb images added
2020-11-26 readme 3d model link
2021-04-08 finalize pinout diagram
2021-04-08 update readme with pinout diagram
